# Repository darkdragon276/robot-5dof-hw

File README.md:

# Driver-servo-esp32-curcuit
thesis's hardware

## Hardware

### Schematics

### PCB Layout

#### Top side

#### Back side

### 3D

#### Top side

#### Back side

### Gerber

Version 1.0

- [Gerber V1.0](./assets/DS-ESP32-ver1.0.zip)

### Remark

This project was in development phase - we will remove this remark after release

# License

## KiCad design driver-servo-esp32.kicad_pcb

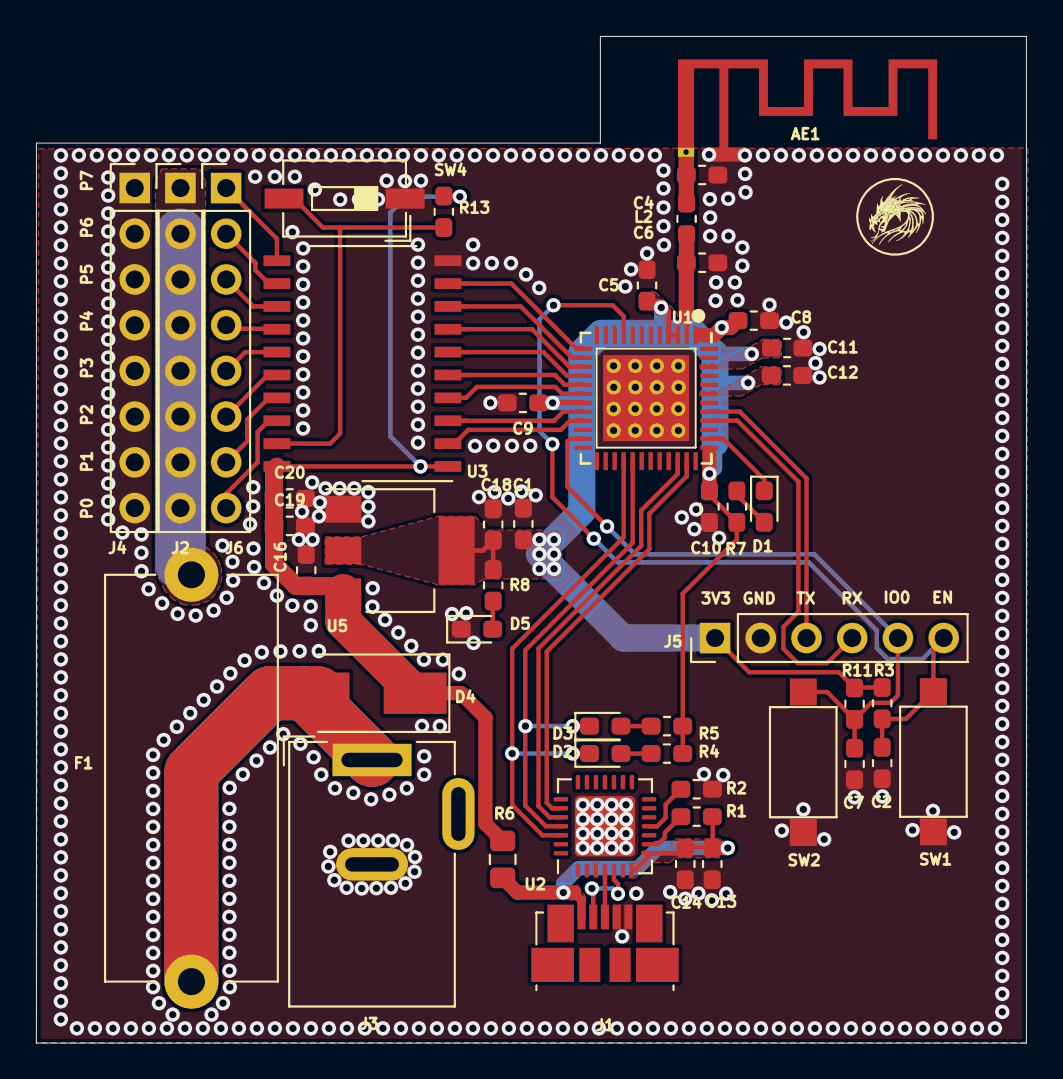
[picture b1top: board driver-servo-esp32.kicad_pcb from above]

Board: 2 copper layers, 55.0 x 55.9 mm, 49 parts (0 on the bottom side), 42 nets.

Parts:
AE1: Antenna_Shield; Texas_SWRA117D_2.4GHz_Right
C1, C13, C16, C18, C19: 10uF; C_0603_1608Metric_Pad1.05x0.95mm_HandSolder
C2, C5, C7, C8, C9, C10, C12, C14, C20: 100nF; C_0603_1608Metric_Pad1.05x0.95mm_HandSolder
C4, C6: TBD; C_0603_1608Metric_Pad1.05x0.95mm_HandSolder
C11: 1uF; C_0603_1608Metric_Pad1.05x0.95mm_HandSolder
D1: STATUS; LED_0603_1608Metric_Pad1.05x0.95mm_HandSolder
D2: TX; LED_0603_1608Metric_Pad1.05x0.95mm_HandSolder
D3: RX; LED_0603_1608Metric_Pad1.05x0.95mm_HandSolder
D4: SS24; D_SMB_Handsoldering
D5: POWER; LED_0603_1608Metric_Pad1.05x0.95mm_HandSolder
F1: Fuse; Fuseholder_Cylinder-5x20mm_Stelvio-Kontek_PTF78_Horizontal_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
J1: USB_B; USB_Micro-B_Molex_47346-0001
J2: VCC; PinHeader_1x08_P2.54mm_Vertical
J3: Jack-DC; BarrelJack_Wuerth_6941xx301002
J4: GND; PinHeader_1x08_P2.54mm_Vertical
J5: ESP_Flash; PinHeader_1x06_P2.54mm_Vertical
J6: PWM; PinHeader_1x08_P2.54mm_Vertical
L2: TBD; L_0603_1608Metric_Pad1.05x0.95mm_HandSolder
OL1: Logo; Nam_logo
R1: 4K7; R_0603_1608Metric_Pad1.05x0.95mm_HandSolder
R2, R3, R11, R13: 10K; R_0603_1608Metric_Pad1.05x0.95mm_HandSolder
R4, R5, R7, R8: 330R; R_0603_1608Metric_Pad1.05x0.95mm_HandSolder
R6: 0R; R_0805_2012Metric_Pad1.15x1.40mm_HandSolder
SW1, SW2: SW_Push; SW_SPST_CK_RS282G05A3
SW4: SW_DIP_x01; SW_DIP_SPSTx01_Slide_6.7x4.1mm_W6.73mm_P2.54mm_LowProfile_J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
U1: ESP32-PICO-D4; QFN-48-1EP_7x7mm_P0.5mm
U2: CP2102N-SHORT; QFN-28-1EP_5x5mm_P0.5mm_EP3.35x3.35mm
U3: AMS1117-3.3; SOT-223-3_TabPin2
U5: 74HC245; SO-20_12.8x7.5mm_P1.27mm

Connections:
+3V3: C1.1, C5.1, C8.1, C9.1, C10.1, C11.1, C12.1, C18.1, J5.1, R3.1, R4.1, R5.1, R7.1, R8.1, R11.1, U1.1, U1.3, U1.4, U1.19, U1.37, U1.43, U1.46, U3.2
+5V: C16.1, C19.1, D4.1, R6.1, R13.1, U3.3, U5.1, U5.20
CP2x_U1CTS: U1.35, U2.23
CP2x_U1RTS: U1.34, U2.24
CP2x_U1RX: D3.1, U1.29, U2.25
CP2x_U1TX: D2.1, U1.28, U2.26
FLASH_EN: C2.1, J5.6, R3.2, SW1.2, U1.9
FLASH_IO0: C7.1, J5.5, R11.2, SW2.2, U1.23
FLASH_U0RX: J5.4, U1.40
FLASH_U0TX: J5.3, U1.41
GND: AE1.1, C1.2, C2.2, C4.2, C5.2, C6.2, C7.2, C8.2, C9.2, C10.2, C11.2, C12.2, C13.2, C14.2, C16.2, C18.2, C19.2, D5.1, J1.4, J1.5, J3.2, J4.1, J4.2, J4.3, J4.4, J4.5, J4.6, J4.7, J4.8, J5.2, R2.1, SW1.1, SW2.1, SW4.1, U1.49, U2.3, U2.29, U3.1, U5.10
LED_STT: D1.1, U1.38
unnamed: AE1.2, C4.1, L2.1
unnamed: C6.1, L2.2, U1.2
unnamed: D1.2, R7.2
unnamed: D2.2, R4.2
unnamed: D3.2, R5.2
unnamed: D5.2, R8.2
unnamed: F1.1, J2.1, J2.2, J2.3, J2.4, J2.5, J2.6, J2.7, J2.8
unnamed: J1.2, U2.5
unnamed: J1.3, U2.4
unnamed: R1.2, U2.9
unnamed: R2.2, U2.11
unnamed: R13.2, SW4.2, U5.19
PWM0: U1.21, U5.2
PWM1: U1.20, U5.3
PWM2: U1.18, U5.4
PWM3: U1.17, U5.5
PWM4: U1.16, U5.6
PWM5: U1.15, U5.7
PWM6: U1.14, U5.8
PWM7: U1.13, U5.9
SERVO0: J6.8, U5.18
SERVO1: J6.7, U5.17
SERVO2: J6.6, U5.16
SERVO3: J6.5, U5.15
SERVO4: J6.4, U5.14
SERVO5: J6.3, U5.13
SERVO6: J6.2, U5.12
SERVO7: J6.1, U5.11
VCC: D4.2, F1.2, J3.1
VCCQ: C13.1, C14.1, J1.1, R1.1, R6.2, U2.7, U2.8

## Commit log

2019-04-14 initial
2019-04-14 schematic backup
2019-04-16 backup
2019-04-17 sche backup
2019-04-20 done pcb
2019-04-20 fix reference of component - pcb
2019-04-21 export gerber
2019-04-21 update assets
2019-05-08 remove auto flash
2019-10-16 update demo
